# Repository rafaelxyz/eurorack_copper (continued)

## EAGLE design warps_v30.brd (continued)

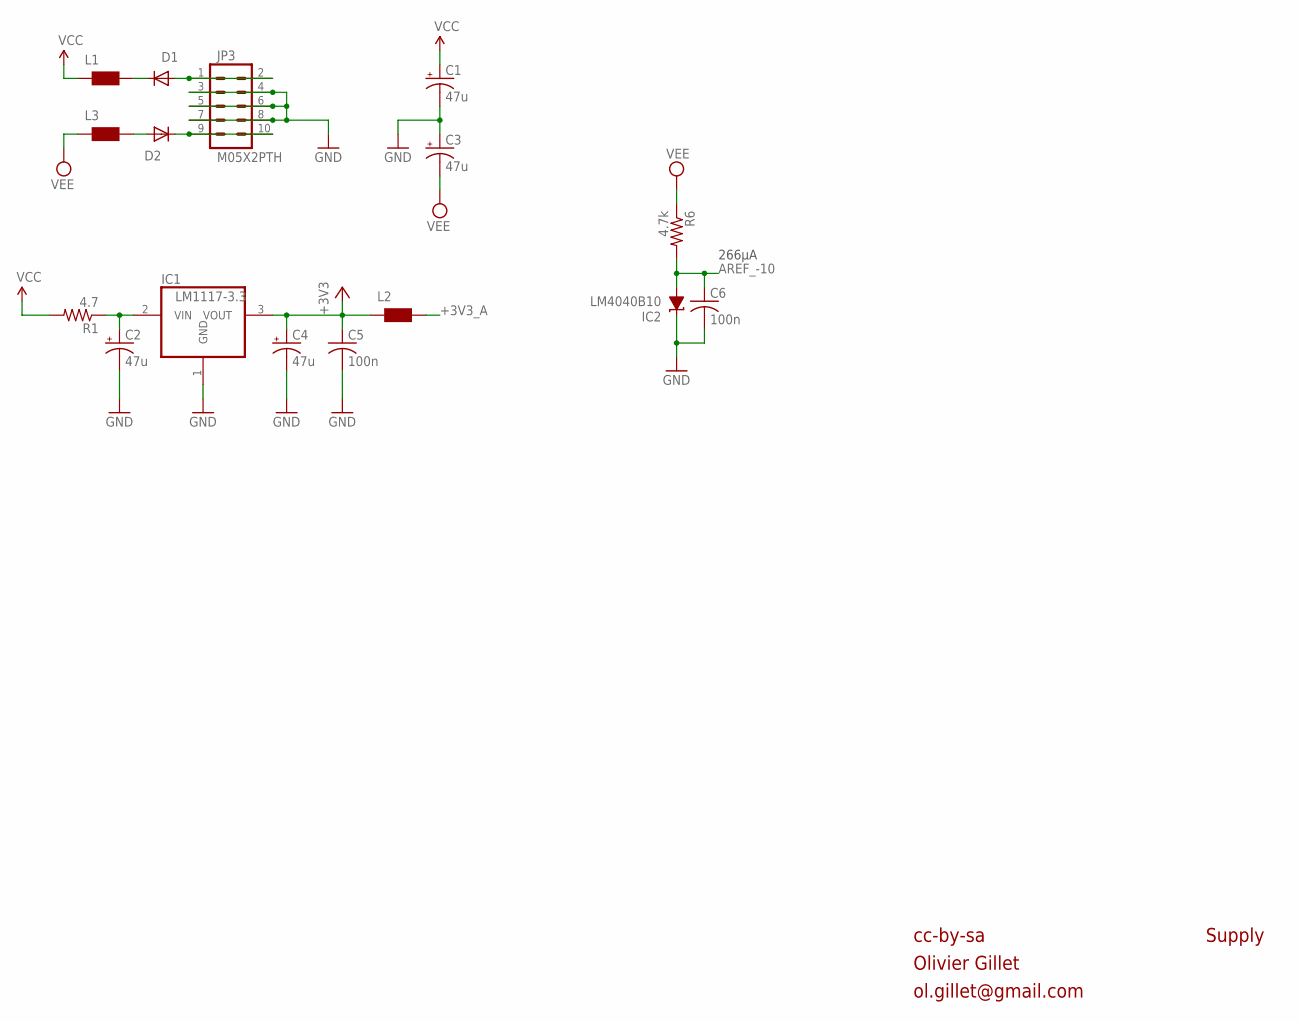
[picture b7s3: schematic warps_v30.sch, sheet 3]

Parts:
C1, C2, C3, C4: 47u; PANASONIC_D
C5, C6: 100n; C0603
D1, D2: 1N5819HW; SOD123
IC1: LM1117-3.3; TO252
IC2: LM4040B10; DBZ_R-PDSO-G3
JP3: M05X2PTH; AVR_ICSP
L1, L2, L3: WE-CBF_0603; 0603
R1: 4.7; R1206
R6: 4.7k; R0603

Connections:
+3V3: C4.+, C5.1, IC1.3 (VOUT), L2.1; also elsewhere on the board
+3V3_A: L2.2; also elsewhere on the board
AREF_-10: C6.1, IC2.2 (A), R6.2; also elsewhere on the board
GND: C1.-, C2.-, C3.+, C4.-, C5.2, C6.2, IC1.1 (GND), IC2.1 (C), JP3.3, JP3.4, JP3.5, JP3.6, JP3.7, JP3.8; also elsewhere on the board
unnamed: C2.+, IC1.2 (VIN), R1.1
unnamed: D1.C, L1.2
unnamed: D2.A, L3.2
unnamed: D1.A, JP3.1, JP3.2
unnamed: D2.C, JP3.9, JP3.10
VCC: C1.+, L1.1, R1.2; also elsewhere on the board
VEE: C3.-, L3.1, R6.1; also elsewhere on the board

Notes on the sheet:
266µA
cc-by-sa
Olivier Gillet
ol.gillet@gmail.com
Supply

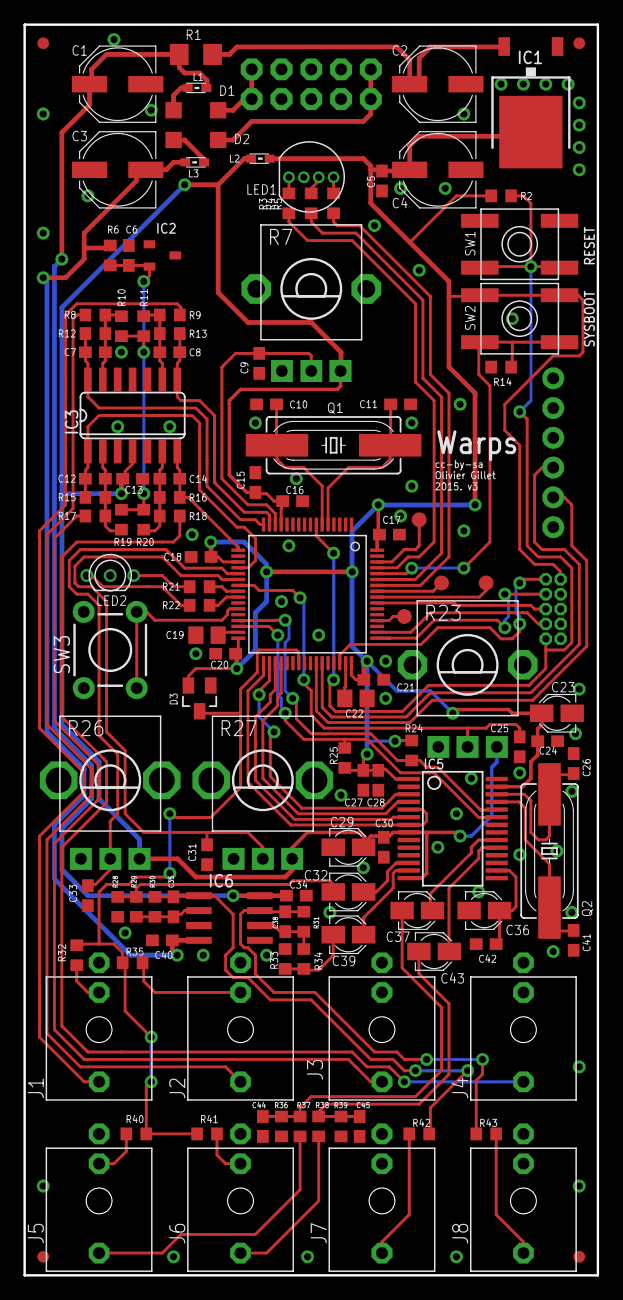
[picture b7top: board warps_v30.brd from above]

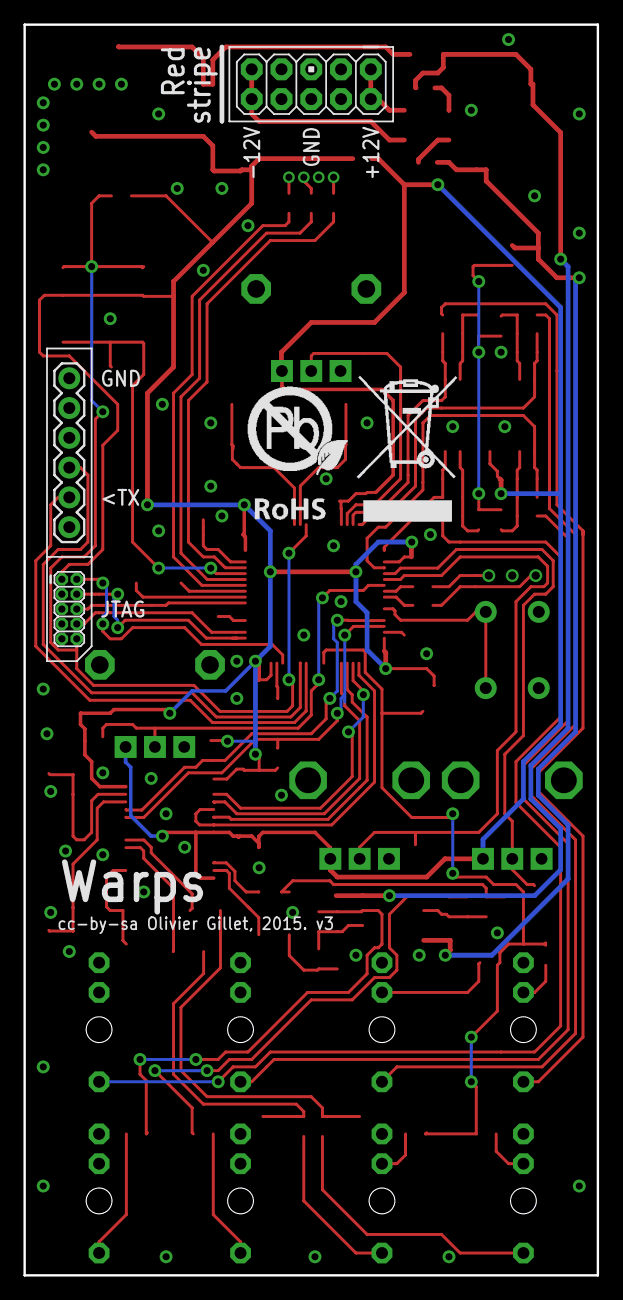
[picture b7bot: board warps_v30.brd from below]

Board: 2 copper layers, 48.9 x 106.7 mm, 127 parts (4 on the bottom side), 84 nets.

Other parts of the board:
U$2: ROHS_BIG

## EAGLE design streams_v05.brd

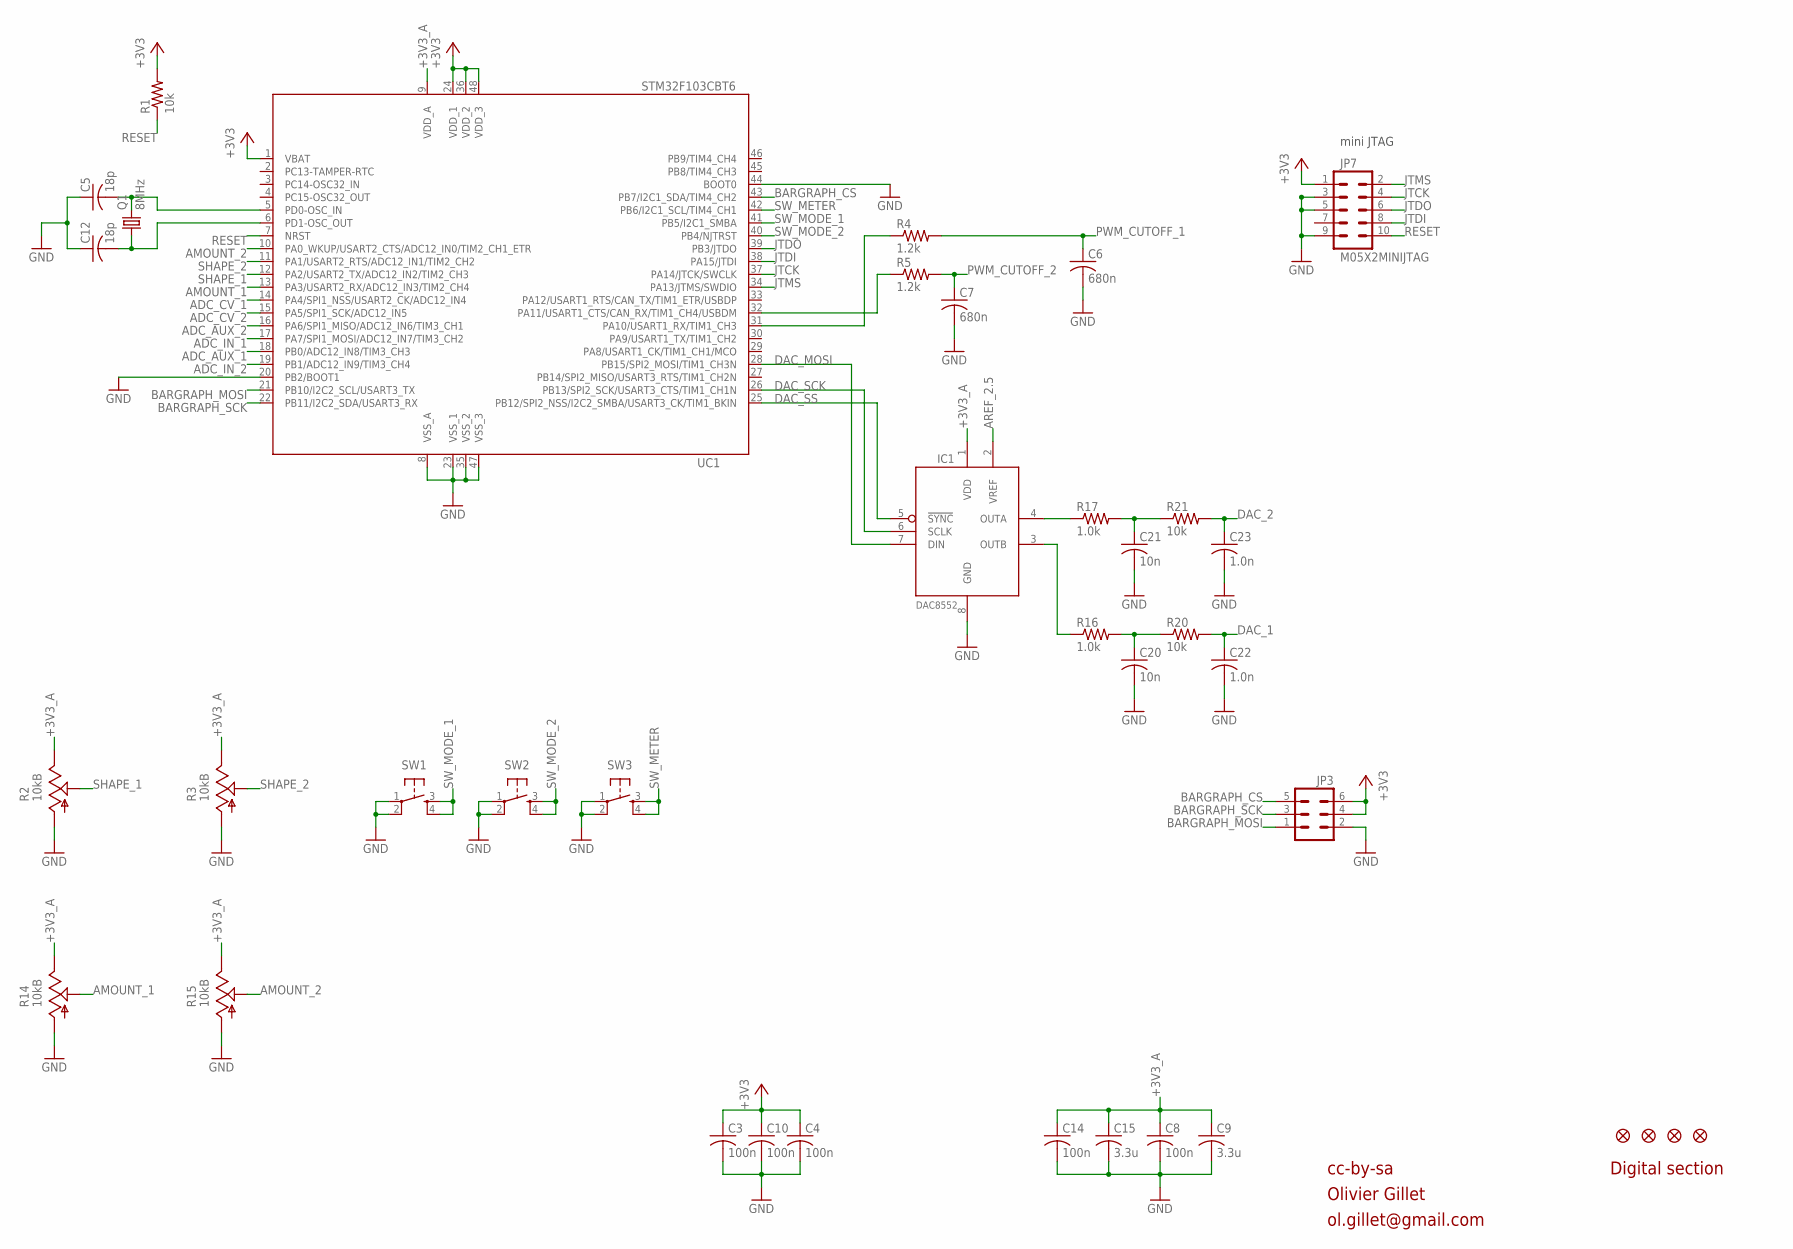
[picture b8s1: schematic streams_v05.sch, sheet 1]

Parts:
C3, C4, C8, C10, C14: 100n; C0603
C5, C12: 18p; C0603
C6, C7: 680n; C0603
C9, C15: 3.3u; C0603
C20, C21: 10n; C0603
C22, C23: 1.0n; C0603
IC1: DAC8552; MSOP-8
JP1, JP2, JP4, JP5: FIDUCIAL1X2; FIDUCIAL-1X2
JP3: M03X2BOTTOM; 2X3_BOTTOM
JP7: M05X2MINIJTAG; 2X5-1.27
Q1: 8MHz; HC49UP
R1, R20, R21: 10k; R0603
R2, R3, R14, R15: 10kB; ALPS_POT_VERTICAL_PS
R4, R5: 1.2k; R0603
R16, R17: 1.0k; R0603
SW1, SW2, SW3: TAC_SWITCHPTH; TACTILE-PTH
UC1: STM32F103CBT6; LQFP48

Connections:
+3V3: C3.1, C4.1, C10.1, JP3.4, JP3.6, JP7.1, R1.2, UC1.1 (VBAT), UC1.24 (VDD_1), UC1.36 (VDD_2), UC1.48 (VDD_3); also elsewhere on the board
+3V3_A: C8.1, C9.1, C14.1, C15.1, IC1.1 (VDD), R2.P$1 (E), R3.P$1 (E), R14.P$1 (E), R15.P$1 (E), UC1.9 (VDD_A); also elsewhere on the board
ADC_AUX_1: UC1.18 (PB0/ADC12_IN8/TIM3_CH3); also elsewhere on the board
ADC_AUX_2: UC1.16 (PA6/SPI1_MISO/ADC12_IN6/TIM3_CH1); also elsewhere on the board
ADC_CV_1: UC1.14 (PA4/SPI1_NSS/USART2_CK/ADC12_IN4); also elsewhere on the board
ADC_CV_2: UC1.15 (PA5/SPI1_SCK/ADC12_IN5); also elsewhere on the board
ADC_IN_1: UC1.17 (PA7/SPI1_MOSI/ADC12_IN7/TIM3_CH2); also elsewhere on the board
ADC_IN_2: UC1.19 (PB1/ADC12_IN9/TIM3_CH4); also elsewhere on the board
AMOUNT_1: R14.P$2 (S), UC1.13 (PA3/USART2_RX/ADC12_IN3/TIM2_CH4)
AMOUNT_2: R15.P$2 (S), UC1.10 (PA0_WKUP/USART2_CTS/ADC12_IN0/TIM2_CH1_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)
AREF_2.5: IC1.2 (VREF); also elsewhere on the board
BARGRAPH_CS: JP3.5, UC1.43 (PB7/I2C1_SDA/TIM4_CH2)
BARGRAPH_MOSI: JP3.1, UC1.21 (PB10/I2C2_SCL/USART3_TX)
BARGRAPH_SCK: JP3.3, UC1.22 (PB11/I2C2_SDA/USART3_RX)
DAC_1: C22.1, R20.2; also elsewhere on the board
DAC_2: C23.1, R21.2; also elsewhere on the board
DAC_MOSI: IC1.7 (DIN), UC1.28 (PB15/SPI2_MOSI/TIM1_CH3N)
DAC_SCK: IC1.6 (SCLK), UC1.26 (PB13/SPI2_SCK/USART3_CTS/TIM1_CH1N)
DAC_SS: IC1.5 (!SYNC), UC1.25 (PB12/SPI2_NSS/I2C2_SMBA/USART3_CK/TIM1_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)
GND: C3.2, C4.2, C5.1, C6.2, C7.2, C8.2, C9.2, C10.2, C12.1, C14.2, C15.2, C20.2, C21.2, C22.2, C23.2, IC1.8 (GND), JP3.2, JP7.3, JP7.5, JP7.9, R2.P$3 (A), R3.P$3 (A), R14.P$3 (A), R15.P$3 (A), SW1.1, SW1.2, SW2.1, SW2.2, SW3.1, SW3.2, UC1.8 (VSS_A), UC1.20 (PB2/BOOT1), UC1.23 (VSS_1), UC1.35 (VSS_2), UC1.44 (BOOT0), UC1.47 (VSS_3); also elsewhere on the board
JTCK: JP7.4, UC1.37 (PA14/JTCK/SWCLK)
JTDI: JP7.8, UC1.38 (PA15/JTDI)
JTDO: JP7.6, UC1.39 (PB3/JTDO)
JTMS: JP7.2, UC1.34 (PA13/JTMS/SWDIO)
unnamed: C5.2, Q1.2, UC1.5 (PD0-OSC_IN)
unnamed: C12.2, Q1.1, UC1.6 (PD1-OSC_OUT)
unnamed: IC1.4 (OUTA), R17.1
unnamed: IC1.3 (OUTB), R16.1
unnamed: C21.1, R17.2, R21.1
unnamed: C20.1, R16.2, R20.1
unnamed: R5.1, UC1.32 (PA11/USART1_CTS/CAN_RX/TIM1_CH4/USBDM)
unnamed: R4.1, UC1.31 (PA10/USART1_RX/TIM1_CH3)
PWM_CUTOFF_1: C6.1, R4.2; also elsewhere on the board
PWM_CUTOFF_2: C7.1, R5.2; also elsewhere on the board
RESET: JP7.10, R1.1, UC1.7 (NRST)
SHAPE_1: R2.P$2 (S), UC1.12 (PA2/USART2_TX/ADC12_IN2/TIM2_CH3)
SHAPE_2: R3.P$2 (S), UC1.11 (PA1/USART2_RTS/ADC12_IN1/TIM2_CH2)
SW_METER: SW3.3, SW3.4, UC1.42 (PB6/I2C1_SCL/TIM4_CH1)
SW_MODE_1: SW1.3, SW1.4, UC1.41 (PB5/I2C1_SMBA)
SW_MODE_2: SW2.3, SW2.4, UC1.40 (PB4/NJTRST)

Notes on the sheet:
cc-by-sa
Olivier Gillet
ol.gillet@gmail.com
Digital section
mini JTAG

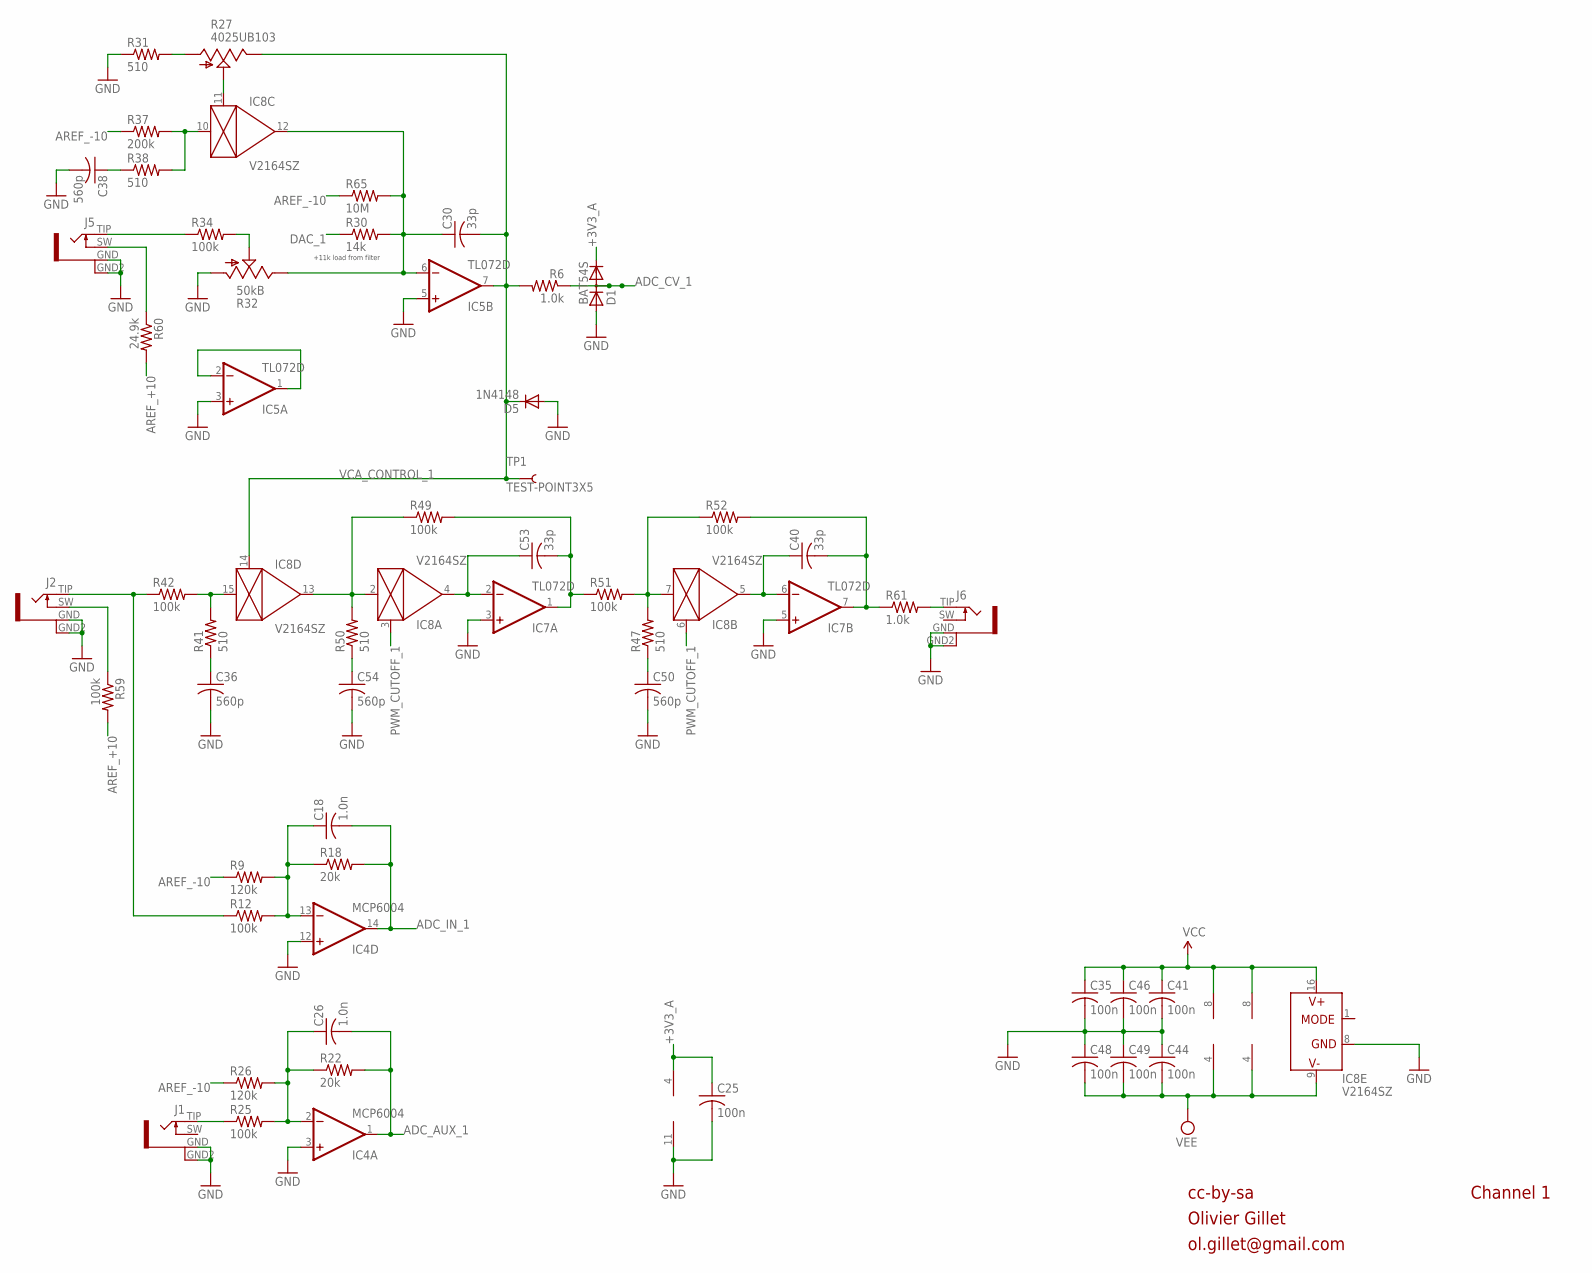
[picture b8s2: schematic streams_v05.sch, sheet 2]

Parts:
C18, C26: 1.0n; C0603
C25, C35, C41, C44, C46, C48, C49: 100n; C0603
C30, C40, C53: 33p; C0603
C36, C38, C50, C54: 560p; C0603
D1: BAT54S; SOT23
D5: 1N4148; SOD323-W
IC4: MCP6004; SO14
IC5, IC7: TL072D; SO08
IC8: V2164SZ; SOIC16N
J1, J2, J5, J6: PJ301WQP; WQP_PJ_301BM_WIDER
R6, R61: 1.0k; R0603
R9, R26: 120k; R0603
R12, R25, R34, R42, R49, R51, R52, R59: 100k; R0603
R18, R22: 20k; R0603
R27: 4025UB103; ALPS_POT_VERTICAL
R30: 14k; R0603
R31, R38, R41, R47, R50: 510; R0603
R32: 50kB; ALPS_POT_VERTICAL_PS
R37: 200k; R0603
R60: 24.9k; R0603
R65: 10M; R0603
TP1: TEST-POINT3X5; PAD.03X.05

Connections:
+3V3_A: C25.1, D1.2 (C), IC4.4 (V+); also elsewhere on the board
ADC_AUX_1: C26.2, IC4.1 (OUT), R22.2; also elsewhere on the board
ADC_CV_1: D1.3 (AC), R6.1; also elsewhere on the board
ADC_IN_1: C18.2, IC4.14 (OUT), R18.2; also elsewhere on the board
AREF_+5: J2.SW (3), R59.1
AREF_+10: R59.2, R60.2; also elsewhere on the board
AREF_-10: R9.1, R26.1, R37.1, R65.1; also elsewhere on the board
DAC_1: R30.1; also elsewhere on the board
FB_CURRENT1: IC8.10 (IN), R37.2, R38.2
FB_CURRENT2: IC8.15 (IN), R41.2, R42.2
GND: C25.2, C35.2, C36.2, C38.2, C41.2, C44.1, C46.2, C48.1, C49.1, C50.2, C54.2, D1.1 (A), D5.A, IC4.3 (+IN), IC4.11 (V-), IC4.12 (+IN), IC5.3 (+IN), IC5.5 (+IN), IC7.3 (+IN), IC7.5 (+IN), IC8.8 (GND), J1.GND (1), J1.GND2 (4), J2.GND (1), J2.GND2 (4), J5.GND (1), J5.GND2 (4), J6.GND (1), J6.GND2 (4), R31.1, R32.P$3 (A); also elsewhere on the board
IN_1: J2.TIP (2), R12.1, R42.1
unnamed: R27.P$3 (A), R31.2
unnamed: C30.1, IC5.6 (-IN), IC8.12 (OUT), R30.2, R32.P$1 (E), R65.2
unnamed: C38.1, R38.1
unnamed: C36.1, R41.1
unnamed: IC5.1 (OUT), IC5.2 (-IN)
unnamed: J5.SW (3), R60.1
unnamed: J5.TIP (2), R34.1
unnamed: IC8.11 (CTRL), R27.P$2 (S)
unnamed: R32.P$2 (S), R34.2
unnamed: C40.1, IC7.6 (-IN), IC8.5 (OUT)
unnamed: C40.2, IC7.7 (OUT), R52.2, R61.1
unnamed: IC8.2 (IN), IC8.13 (OUT), R49.1, R50.2
unnamed: J1.TIP (2), R25.1
unnamed: C18.1, IC4.13 (-IN), R9.2, R12.2, R18.1
unnamed: C26.1, IC4.2 (-IN), R22.1, R25.2, R26.2
unnamed: C53.1, IC7.2 (-IN), IC8.4 (OUT)
unnamed: C53.2, IC7.1 (OUT), R49.2, R51.1
unnamed: IC8.7 (IN), R47.2, R51.2, R52.1
unnamed: C54.1, R50.1
unnamed: C50.1, R47.1
unnamed: J6.TIP (2), R61.2
PWM_CUTOFF_1: IC8.3 (CTRL), IC8.6 (CTRL); also elsewhere on the board
VCA_CONTROL_1: C30.2, D5.C, IC5.7 (OUT), IC8.14 (CTRL), R6.2, R27.P$1 (E), TP1.P$1
VCC: C35.1, C41.1, C46.1, IC5.8 (V+), IC7.8 (V+), IC8.16 (V+); also elsewhere on the board
VEE: C44.2, C48.2, C49.2, IC5.4 (V-), IC7.4 (V-), IC8.9 (V-); also elsewhere on the board

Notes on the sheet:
cc-by-sa
Olivier Gillet
ol.gillet@gmail.com
Channel 1
+11k load from filter

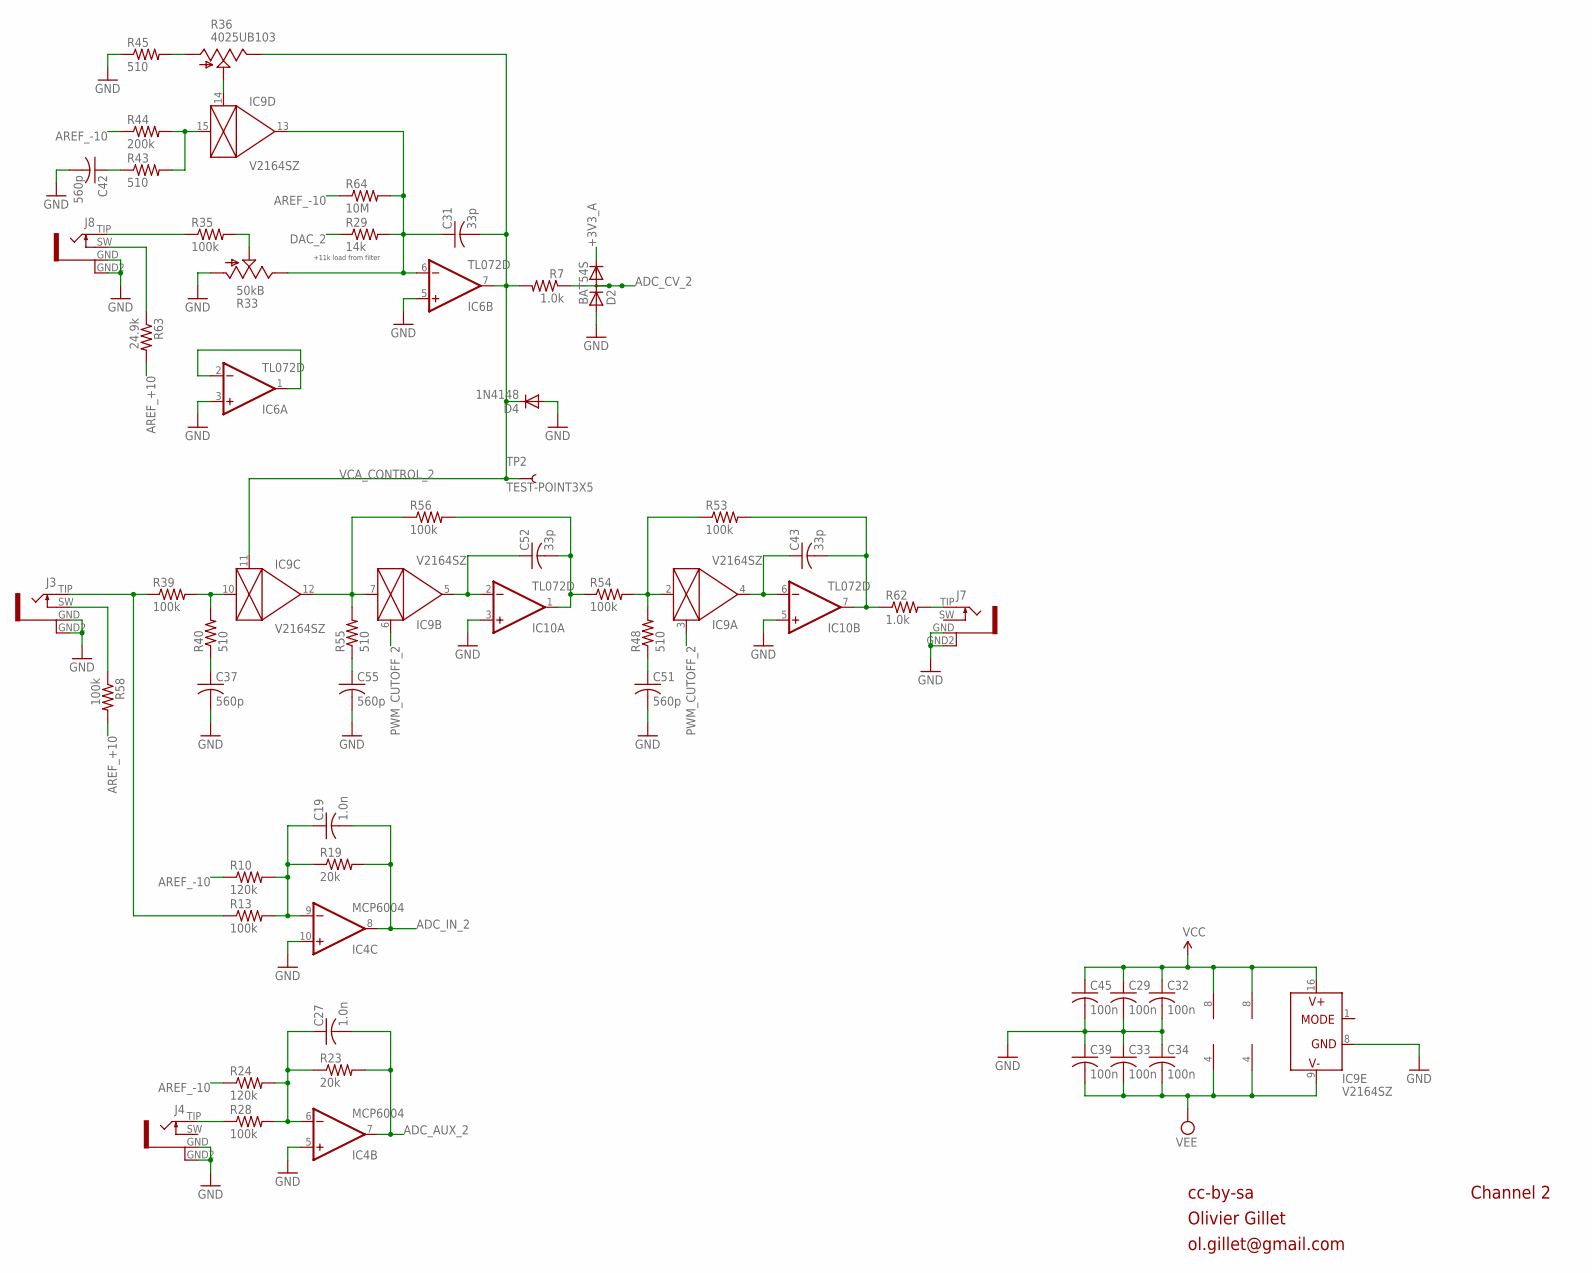
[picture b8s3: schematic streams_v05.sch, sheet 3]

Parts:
C19, C27: 1.0n; C0603
C29, C32, C33, C34, C39, C45: 100n; C0603
C31, C43, C52: 33p; C0603
C37, C42, C51, C55: 560p; C0603
D2: BAT54S; SOT23
D4: 1N4148; SOD323-W
IC4: MCP6004; SO14
IC6, IC10: TL072D; SO08
IC9: V2164SZ; SOIC16N
J3, J4, J7, J8: PJ301WQP; WQP_PJ_301BM_WIDER
R7, R62: 1.0k; R0603
R10, R24: 120k; R0603
R13, R28, R35, R39, R53, R54, R56, R58: 100k; R0603
R19, R23: 20k; R0603
R29: 14k; R0603
R33: 50kB; ALPS_POT_VERTICAL_PS
R36: 4025UB103; ALPS_POT_VERTICAL
R40, R43, R45, R48, R55: 510; R0603
R44: 200k; R0603
R63: 24.9k; R0603
R64: 10M; R0603
TP2: TEST-POINT3X5; PAD.03X.05

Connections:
+3V3_A: D2.2 (C); also elsewhere on the board
ADC_AUX_2: C27.2, IC4.7 (OUT), R23.2; also elsewhere on the board
ADC_CV_2: D2.3 (AC), R7.1; also elsewhere on the board
ADC_IN_2: C19.2, IC4.8 (OUT), R19.2; also elsewhere on the board
AREF_+10: R58.2, R63.2; also elsewhere on the board
AREF_-10: R10.1, R24.1, R44.1, R64.1; also elsewhere on the board
DAC_2: R29.1; also elsewhere on the board
FB_CURRENT3: IC9.10 (IN), R39.2, R40.2
FB_CURRENT4: IC9.15 (IN), R43.2, R44.2
GND: C29.2, C32.2, C33.1, C34.1, C37.2, C39.1, C42.2, C45.2, C51.2, C55.2, D2.1 (A), D4.A, IC4.5 (+IN), IC4.10 (+IN), IC6.3 (+IN), IC6.5 (+IN), IC9.8 (GND), IC10.3 (+IN), IC10.5 (+IN), J3.GND (1), J3.GND2 (4), J4.GND (1), J4.GND2 (4), J7.GND (1), J7.GND2 (4), J8.GND (1), J8.GND2 (4), R33.P$3 (A), R45.1; also elsewhere on the board
IN_2: J3.TIP (2), R13.1, R39.1
unnamed: J8.SW (3), R63.1
unnamed: C37.1, R40.1
unnamed: C31.1, IC6.6 (-IN), IC9.13 (OUT), R29.2, R33.P$1 (E), R64.2
unnamed: C43.1, IC9.4 (OUT), IC10.6 (-IN)
unnamed: C43.2, IC10.7 (OUT), R53.2, R62.1
unnamed: J7.TIP (2), R62.2
unnamed: R36.P$3 (A), R45.2
unnamed: C42.1, R43.1
unnamed: R33.P$2 (S), R35.2
unnamed: J8.TIP (2), R35.1
unnamed: IC6.1 (OUT), IC6.2 (-IN)
unnamed: IC9.14 (CTRL), R36.P$2 (S)
unnamed: J3.SW (3), R58.1
unnamed: C27.1, IC4.6 (-IN), R23.1, R24.2, R28.2
unnamed: J4.TIP (2), R28.1
unnamed: C19.1, IC4.9 (-IN), R10.2, R13.2, R19.1
unnamed: IC9.7 (IN), IC9.12 (OUT), R55.2, R56.1
unnamed: C52.1, IC9.5 (OUT), IC10.2 (-IN)
unnamed: IC9.2 (IN), R48.2, R53.1, R54.2
unnamed: C52.2, IC10.1 (OUT), R54.1, R56.2
unnamed: C55.1, R55.1
unnamed: C51.1, R48.1
PWM_CUTOFF_2: IC9.3 (CTRL), IC9.6 (CTRL); also elsewhere on the board
VCA_CONTROL_2: C31.2, D4.C, IC6.7 (OUT), IC9.11 (CTRL), R7.2, R36.P$1 (E), TP2.P$1
VCC: C29.1, C32.1, C45.1, IC6.8 (V+), IC9.16 (V+), IC10.8 (V+); also elsewhere on the board
VEE: C33.2, C34.2, C39.2, IC6.4 (V-), IC9.9 (V-), IC10.4 (V-); also elsewhere on the board

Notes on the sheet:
cc-by-sa
Olivier Gillet
ol.gillet@gmail.com
Channel 2
+11k load from filter

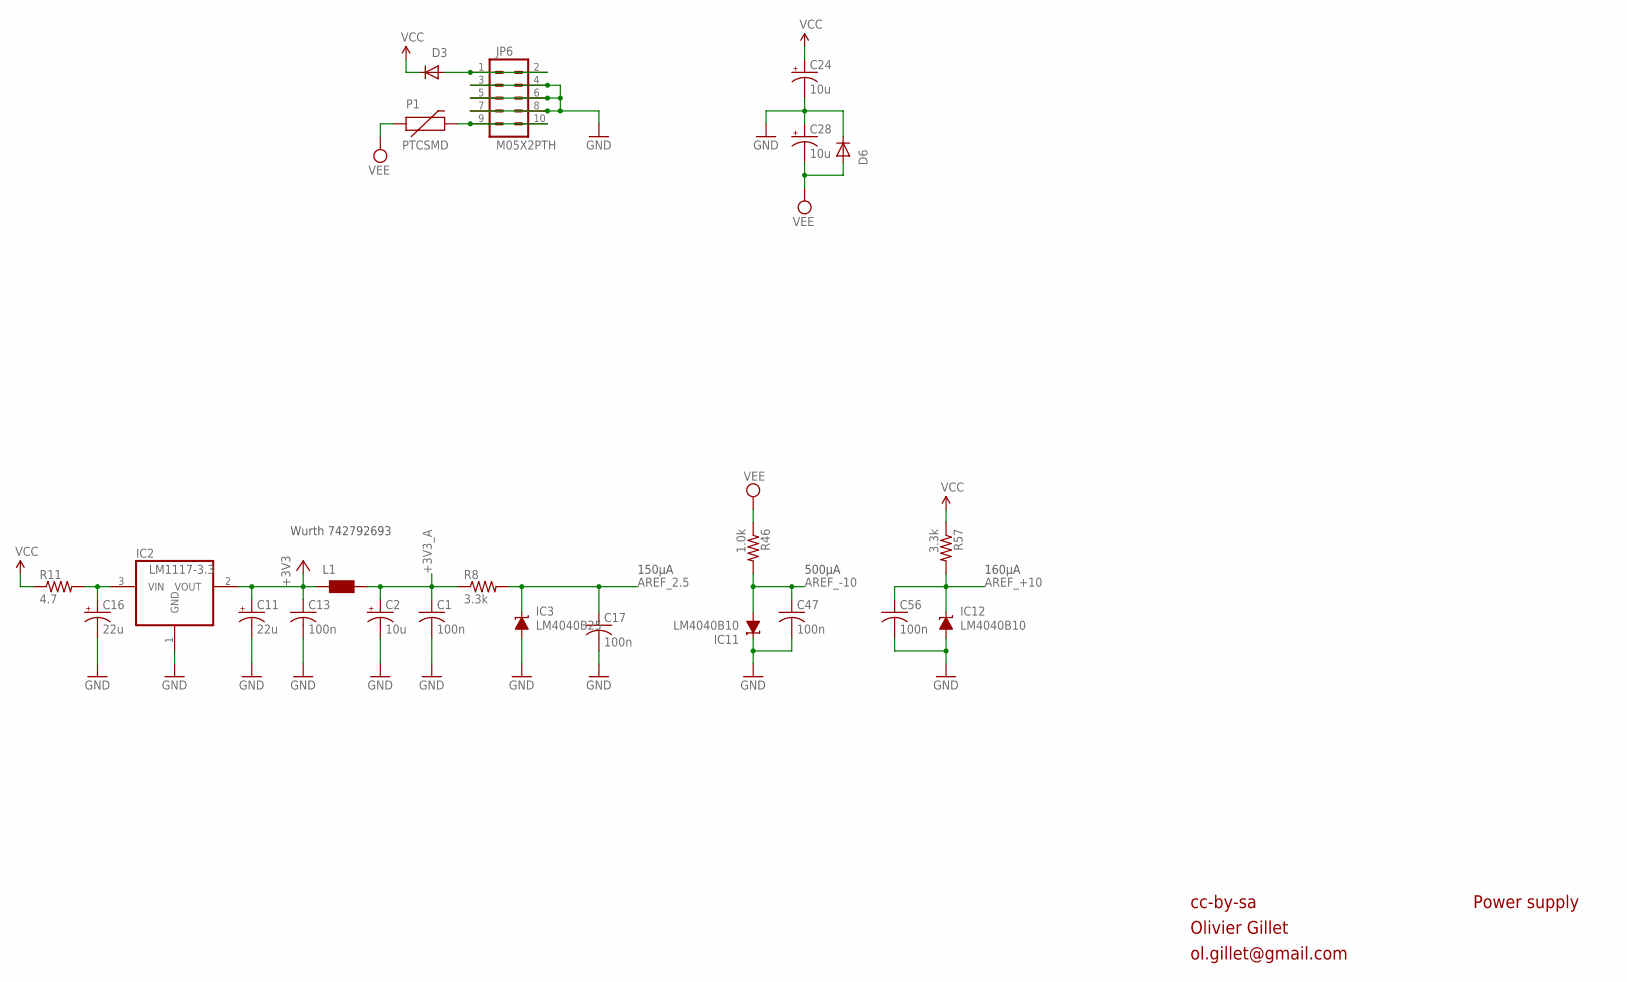
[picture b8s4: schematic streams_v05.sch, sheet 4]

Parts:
C1, C13, C17, C47, C56: 100n; C0603
C2, C24, C28: 10u; PANASONIC_B
C11: 22u; PANASONIC_B
C16: 22u; PANASONIC_C
D3, D6: 1N5819HW; SOD123
IC2: LM1117-3.3; SOT223
IC3: LM4040B25; DBZ_R-PDSO-G3
IC11, IC12: LM4040B10; DBZ_R-PDSO-G3
JP6: M05X2PTH; AVR_ICSP
L1: WE-CBF_0603; 0603
P1: PTCSMD; PTC-1206
R8, R57: 3.3k; R0603
R11: 4.7; R1206
R46: 1.0k; R0603

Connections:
+3V3: C11.+, C13.1, IC2.2 (VOUT), L1.1; also elsewhere on the board
+3V3_A: C1.1, C2.+, L1.2, R8.1; also elsewhere on the board
AREF_2.5: C17.1, IC3.1 (C), R8.2; also elsewhere on the board
AREF_+10: C56.1, IC12.1 (C), R57.2; also elsewhere on the board
AREF_-10: C47.1, IC11.2 (A), R46.2; also elsewhere on the board
GND: C1.2, C2.-, C11.-, C13.2, C16.-, C17.2, C24.-, C28.+, C47.2, C56.2, D6.C, IC2.1 (GND), IC3.2 (A), IC11.1 (C), IC12.2 (A), JP6.3, JP6.4, JP6.5, JP6.6, JP6.7, JP6.8; also elsewhere on the board
unnamed: C16.+, IC2.3 (VIN), R11.2
unnamed: D3.A, JP6.1, JP6.2
unnamed: JP6.9, JP6.10, P1.2
VCC: C24.+, D3.C, R11.1, R57.1; also elsewhere on the board
VEE: C28.-, D6.A, P1.1, R46.1; also elsewhere on the board

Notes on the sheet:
cc-by-sa
Olivier Gillet
ol.gillet@gmail.com
Power supply
500µA
Wurth 742792693
150µA
160µA

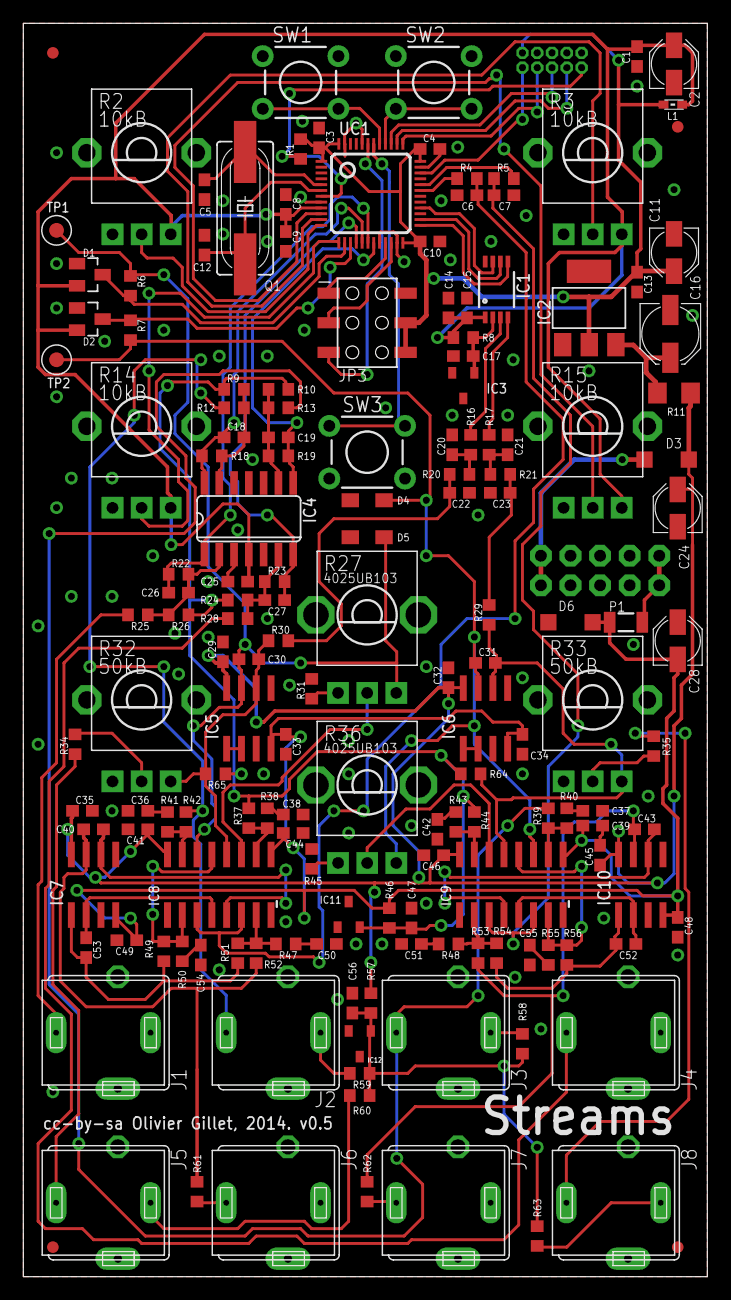
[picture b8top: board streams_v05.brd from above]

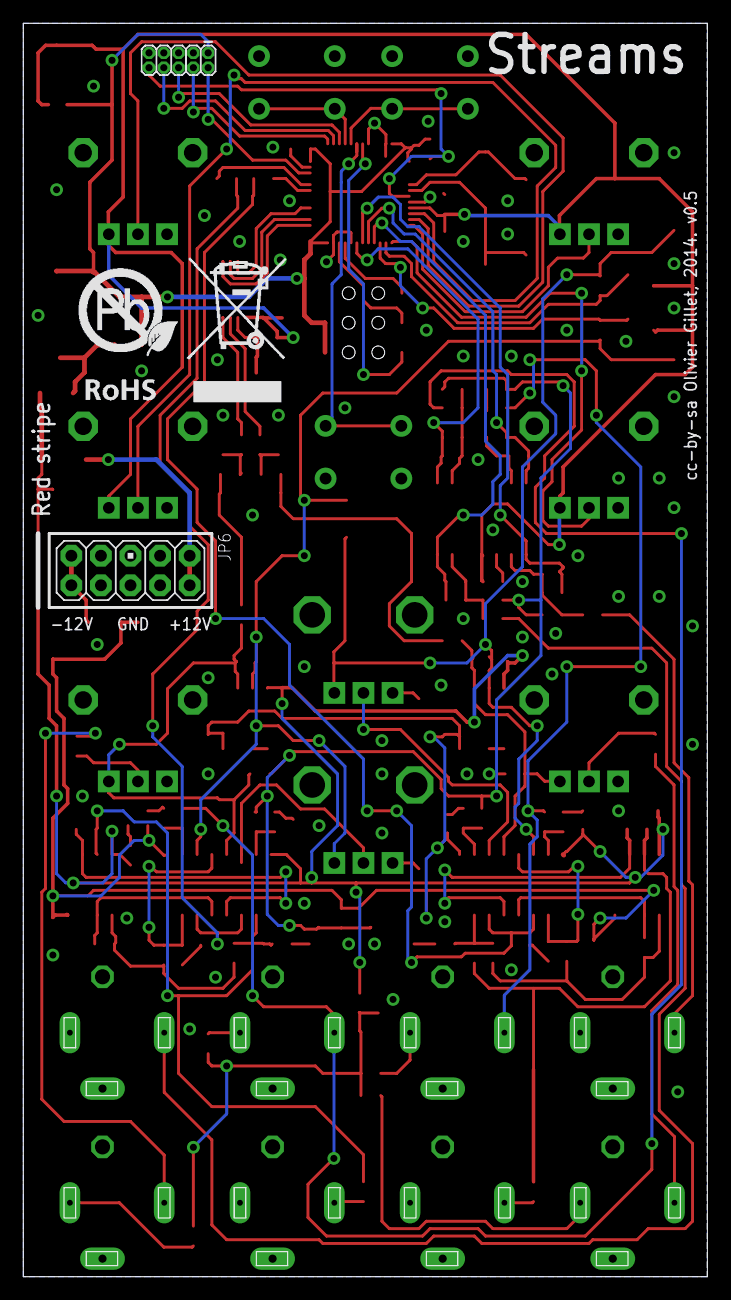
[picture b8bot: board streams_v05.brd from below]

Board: 2 copper layers, 58.7 x 107.6 mm, 164 parts (3 on the bottom side), 99 nets.

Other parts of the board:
U$1: ROHS_BIG

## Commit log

2018-03-27 kinks
2018-05-06 rm originals
2018-08-07 peaks
2019-01-27 shades
2019-01-27 order1
